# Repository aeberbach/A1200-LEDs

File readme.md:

# Amiga 1200 LED assembly

I am far from the first person to make a new A1200 LED board. 

As I built a ReAmiga 1.5 I needed an extra LED board. I could have bought one but making something like this was a pretty good way to end a day of meetings and boring maintenance programming. 

The original used a rectangular lens with a pair of LEDs at its base. I've seen a single LED illuminating a light pipe, also a line of rectangular LEDs with no light pipe. I decided to try 3D printed light pipes.

I have a roll of transparent Prusament PETG. When printed it comes out looking like an ice cube due to all the layer boundaries. The transparent A1200.net case I want to use means this transparent filament is a good match when making mounts for my keyboard and other parts. I found the direction of print really matters - If printed standing "up" then the light does not cross the lines of printing all that well and the LED is dim. If printed flat then the layers transmit light well and the LED is bright.

While the A1200.net case is patterned on later model A1200 cases and uses 15mm rectangular holes for the LEDs, older A1200 cases used 14mm LED holes. It would maybe be possible to print light pipe pieces so that they could be turned over, with 14mm one side and 15mm the other? I have just made two versions for now.

The opaque plastic base aligns and holds the translucent pieces, and blocks the light from crossing from one LED to an adjacent one. There is a recess to allow the SMD component to fit under the translucent pieces. 

PCB manufacture was by JLCPCB. Shipping is by far the most expensive part of this project. I'm using the most economical LEDs I could find on Mouser in 0805 size, the smallest I like to solder by hand. They drop 2.2V and have a maximum current of 20mA. I targeted 15mA and settled on a 180 ohm resistor. Because the green LED is far less bright I used a 120 
ohm resistor there.

Another thing I did was use a 4-pin right angled header instead of soldering wire direct to the PCB. Whenever I have removed an A1200 cover I have not liked the dangling wire. Sometimes I forget it's there and yank the wire. These wire connections break. Also I don't love soldering ordinary PVC-insulated wire to PCBs as the insulation melts and shrinks back. It would be nice to have rolls of PTFE-insulated cable in the right size and color at hand but that's expensive. Instead I made a cable connecting the 5-position mainboard end to the 4-position LED board end. There isn't room to use 5 positions on the board end. 

So how does it look?

I'm happy with that. 

If you want one it may be worth asking me if you're local. If you're not then just buy one from your closest store, many places sell a similar thing and if this is all you're buying the postage might be the biggest cost.

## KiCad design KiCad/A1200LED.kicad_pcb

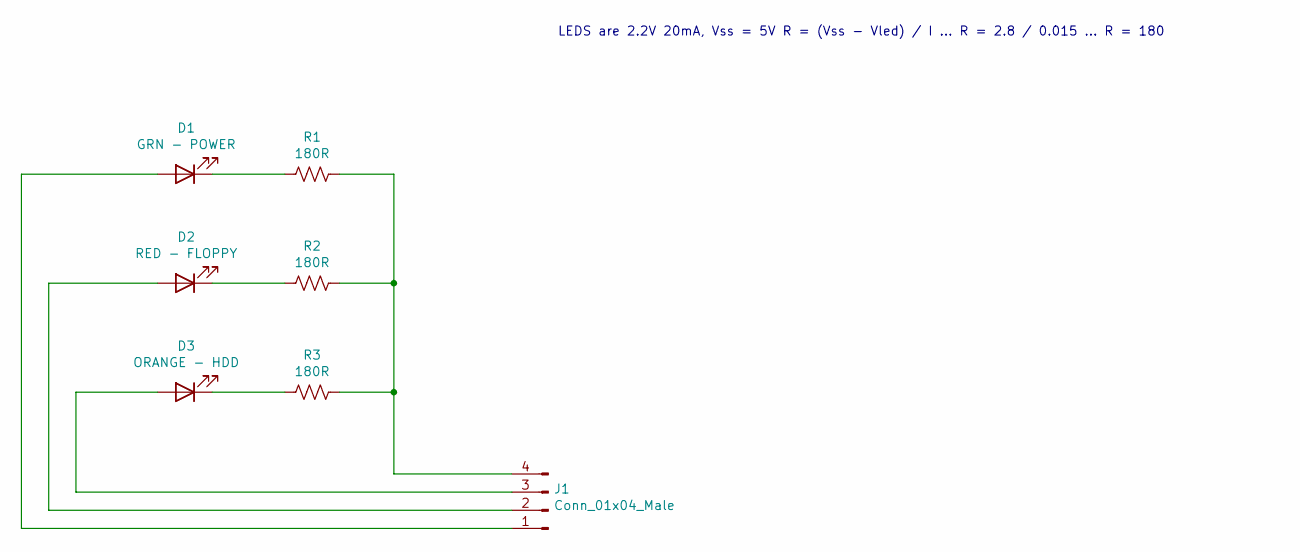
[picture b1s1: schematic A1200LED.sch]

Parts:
D1: GRN - POWER; LED_0805_2012Metric_Pad1.15x1.40mm_HandSolder
D2: RED - FLOPPY; LED_0805_2012Metric_Pad1.15x1.40mm_HandSolder
D3: ORANGE - HDD; LED_0805_2012Metric_Pad1.15x1.40mm_HandSolder
J1: Conn_01x04_Male; PinHeader_1x04_P2.54mm_Vertical
R1, R2, R3: 180R; R_0805_2012Metric_Pad1.20x1.40mm_HandSolder

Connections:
unnamed: D1.1 (K), R1.2
unnamed: D1.2 (A), J1.1
unnamed: D2.1 (K), R2.2
unnamed: D2.2 (A), J1.2
unnamed: D3.1 (K), R3.2
unnamed: D3.2 (A), J1.3
unnamed: J1.4, R1.1, R2.1, R3.1

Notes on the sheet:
LEDS are 2.2V 20mA, Vss = 5V R = (Vss - Vled) / I ... R = 2.8 / 0.015 ... R = 180

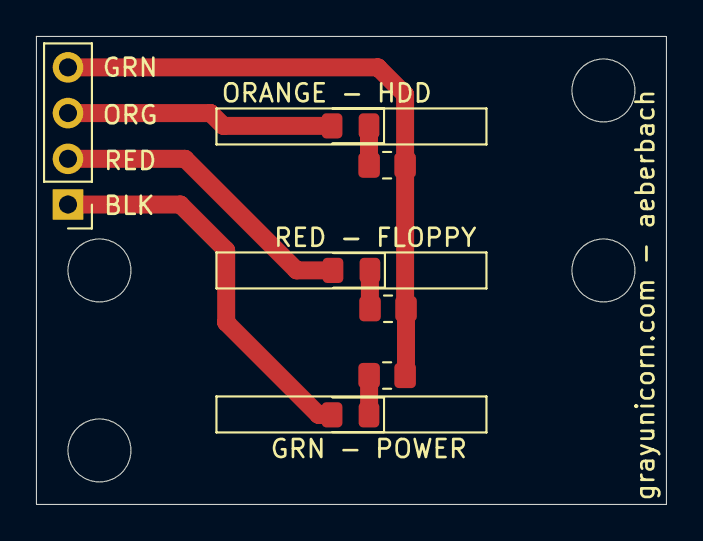
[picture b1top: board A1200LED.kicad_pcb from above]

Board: 2 copper layers, 35.0 x 26.0 mm, 7 parts (0 on the bottom side), 7 nets.

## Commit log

2021-08-16 Complete
2021-08-16 Images
2021-08-16 License, gitignore
2021-08-16 typo
2021-08-17 Fixed design of parts (better in original C= case)
2021-08-17 Didn't want to commit backup files
